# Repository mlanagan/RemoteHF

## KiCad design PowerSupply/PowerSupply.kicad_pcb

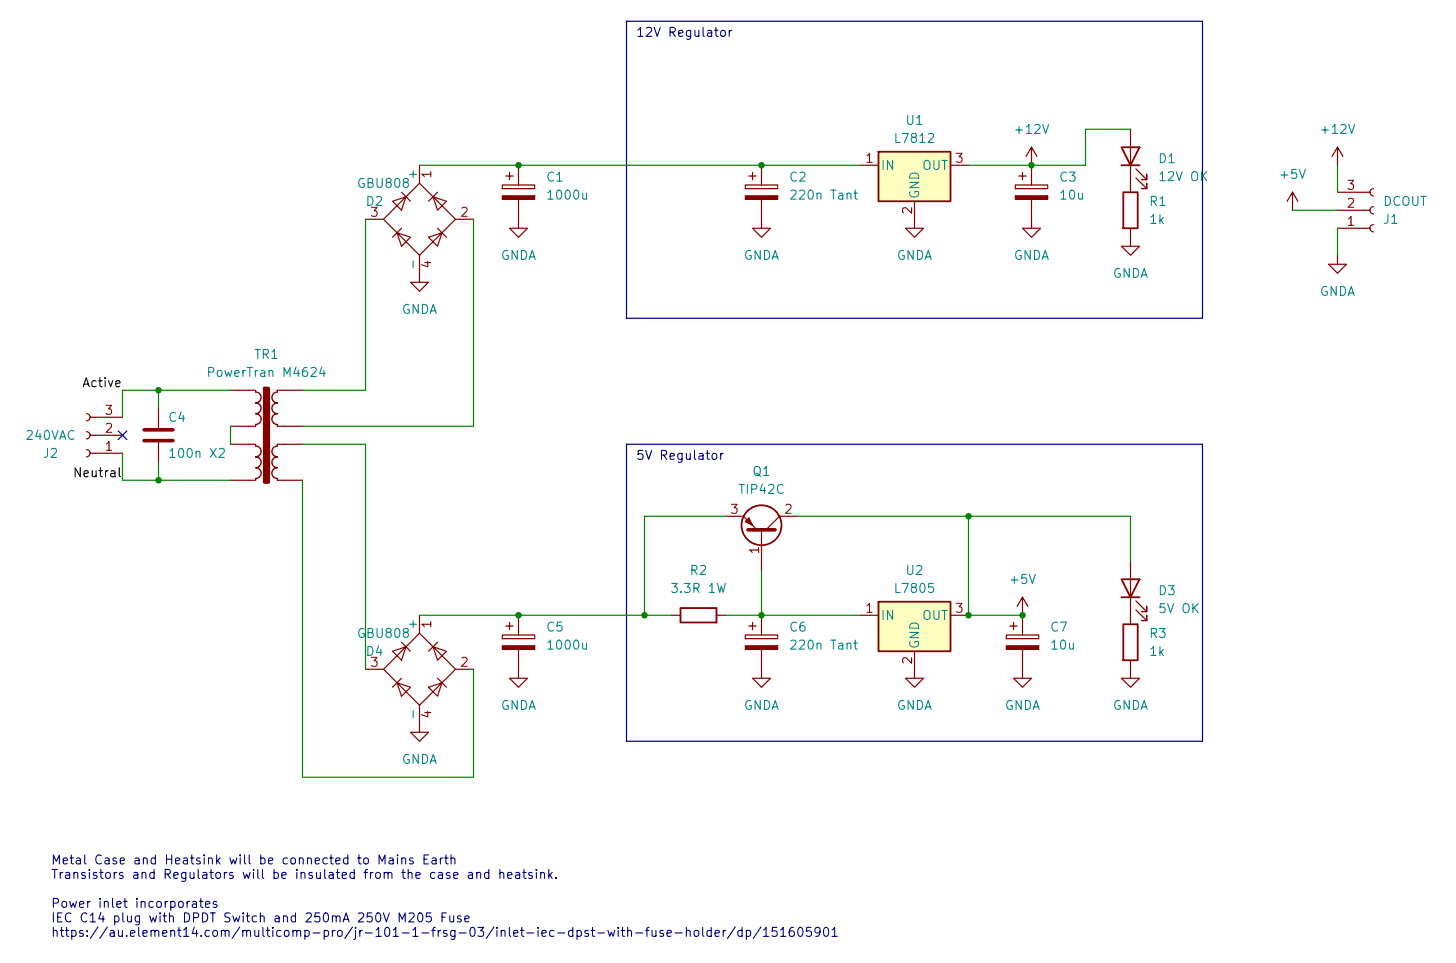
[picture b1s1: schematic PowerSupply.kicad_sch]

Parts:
C1, C5: 1000u; CP_Radial_D13.0mm_P5.00mm
C2, C6: 220n Tant; CP_EIA-3216-18_Kemet-A
C3, C7: 10u; CP_Elec_5x5.7
C4: 100n X2; C_Rect_L18.0mm_W5.0mm_P15.00mm_FKS3_FKP3
D1: 12V OK; LED_0805_2012Metric
D2, D4: GBU808; Diode_Bridge_Vishay_GBU
D3: 5V OK; LED_0805_2012Metric
J1: DCOUT; ScrewTermConnector 1x3
J2: 240VAC; Molex_KK-396_5273-03A_1x03_P3.96mm_Vertical
Q1: TIP42C; TO-220-3_Vertical
R1, R3: 1k; R_0805_2012Metric
R2: 3.3R 1W; R_2512_6332Metric
TR1: PowerTran M4624
U1: L7812; TO-220-3_Vertical
U2: L7805; TO-220-3_Vertical

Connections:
+5V: C7.1, D3.2 (A), J1.2, Q1.2 (C), U2.3 (OUT)
+12V: C3.1, D1.2 (A), J1.3, U1.3 (OUT)
/Active: C4.1, J2.3, TR1.1
/Neutral: C4.2, J2.1, TR1.4
GNDA: C1.2, C2.2, C3.2, C5.2, C6.2, C7.2, D2.4 (-), D4.4 (-), J1.1, R1.2, R3.2, U1.2 (GND), U2.2 (GND)
unnamed: D1.1 (K), R1.1
unnamed: C1.1, C2.1, D2.1 (+), U1.1 (IN)
unnamed: D2.2, TR1.7
unnamed: D2.3, TR1.8
unnamed: D3.1 (K), R3.1
unnamed: C5.1, D4.1 (+), Q1.3 (E), R2.1
unnamed: D4.2, TR1.5
unnamed: D4.3, TR1.6
unnamed: C6.1, Q1.1 (B), R2.2, U2.1 (IN)
unnamed: TR1.2, TR1.3

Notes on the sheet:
Metal Case and Heatsink will be connected to Mains Earth Transistors and Regulators will be insulated from the case and heatsink. Power inlet incorporates IEC C14 plug with DPDT Switch and 250mA 250V M205 Fuse https://au.element14.com/multicomp-pro/jr-101-1-frsg-03/inlet-iec-dpst-with-fuse-holder/d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
12V Regulator
5V Regulator

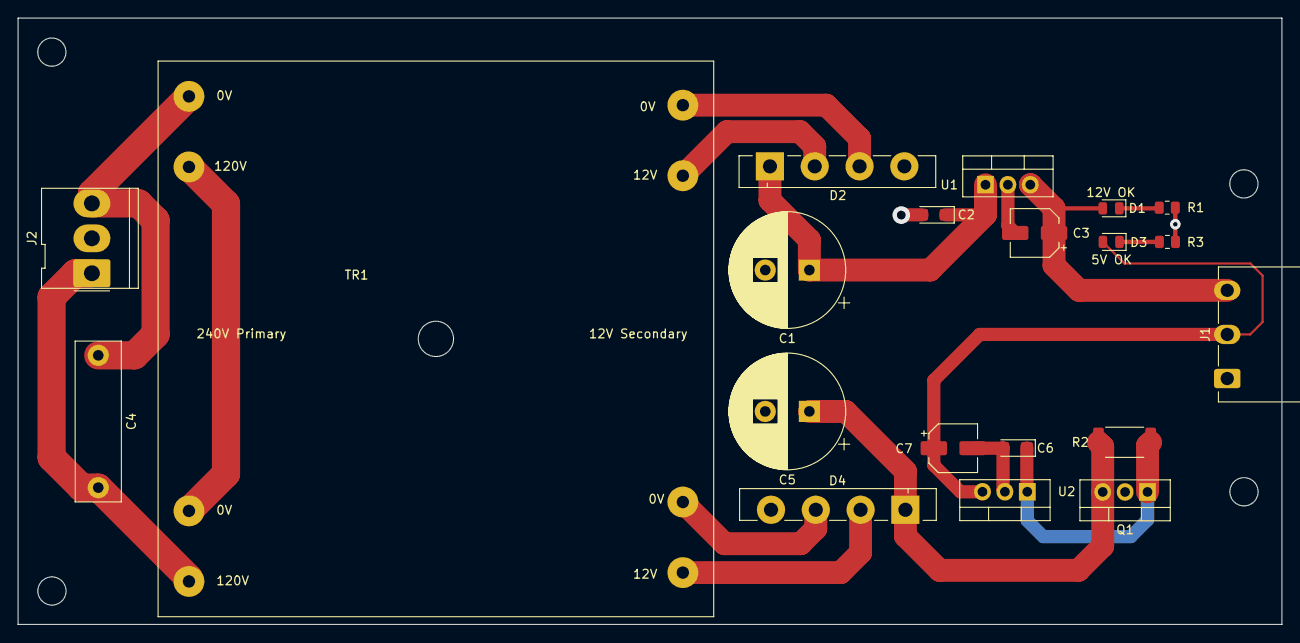
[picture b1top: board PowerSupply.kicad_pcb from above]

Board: 2 copper layers, 143.3 x 68.8 mm, 20 parts (0 on the bottom side), 15 nets.

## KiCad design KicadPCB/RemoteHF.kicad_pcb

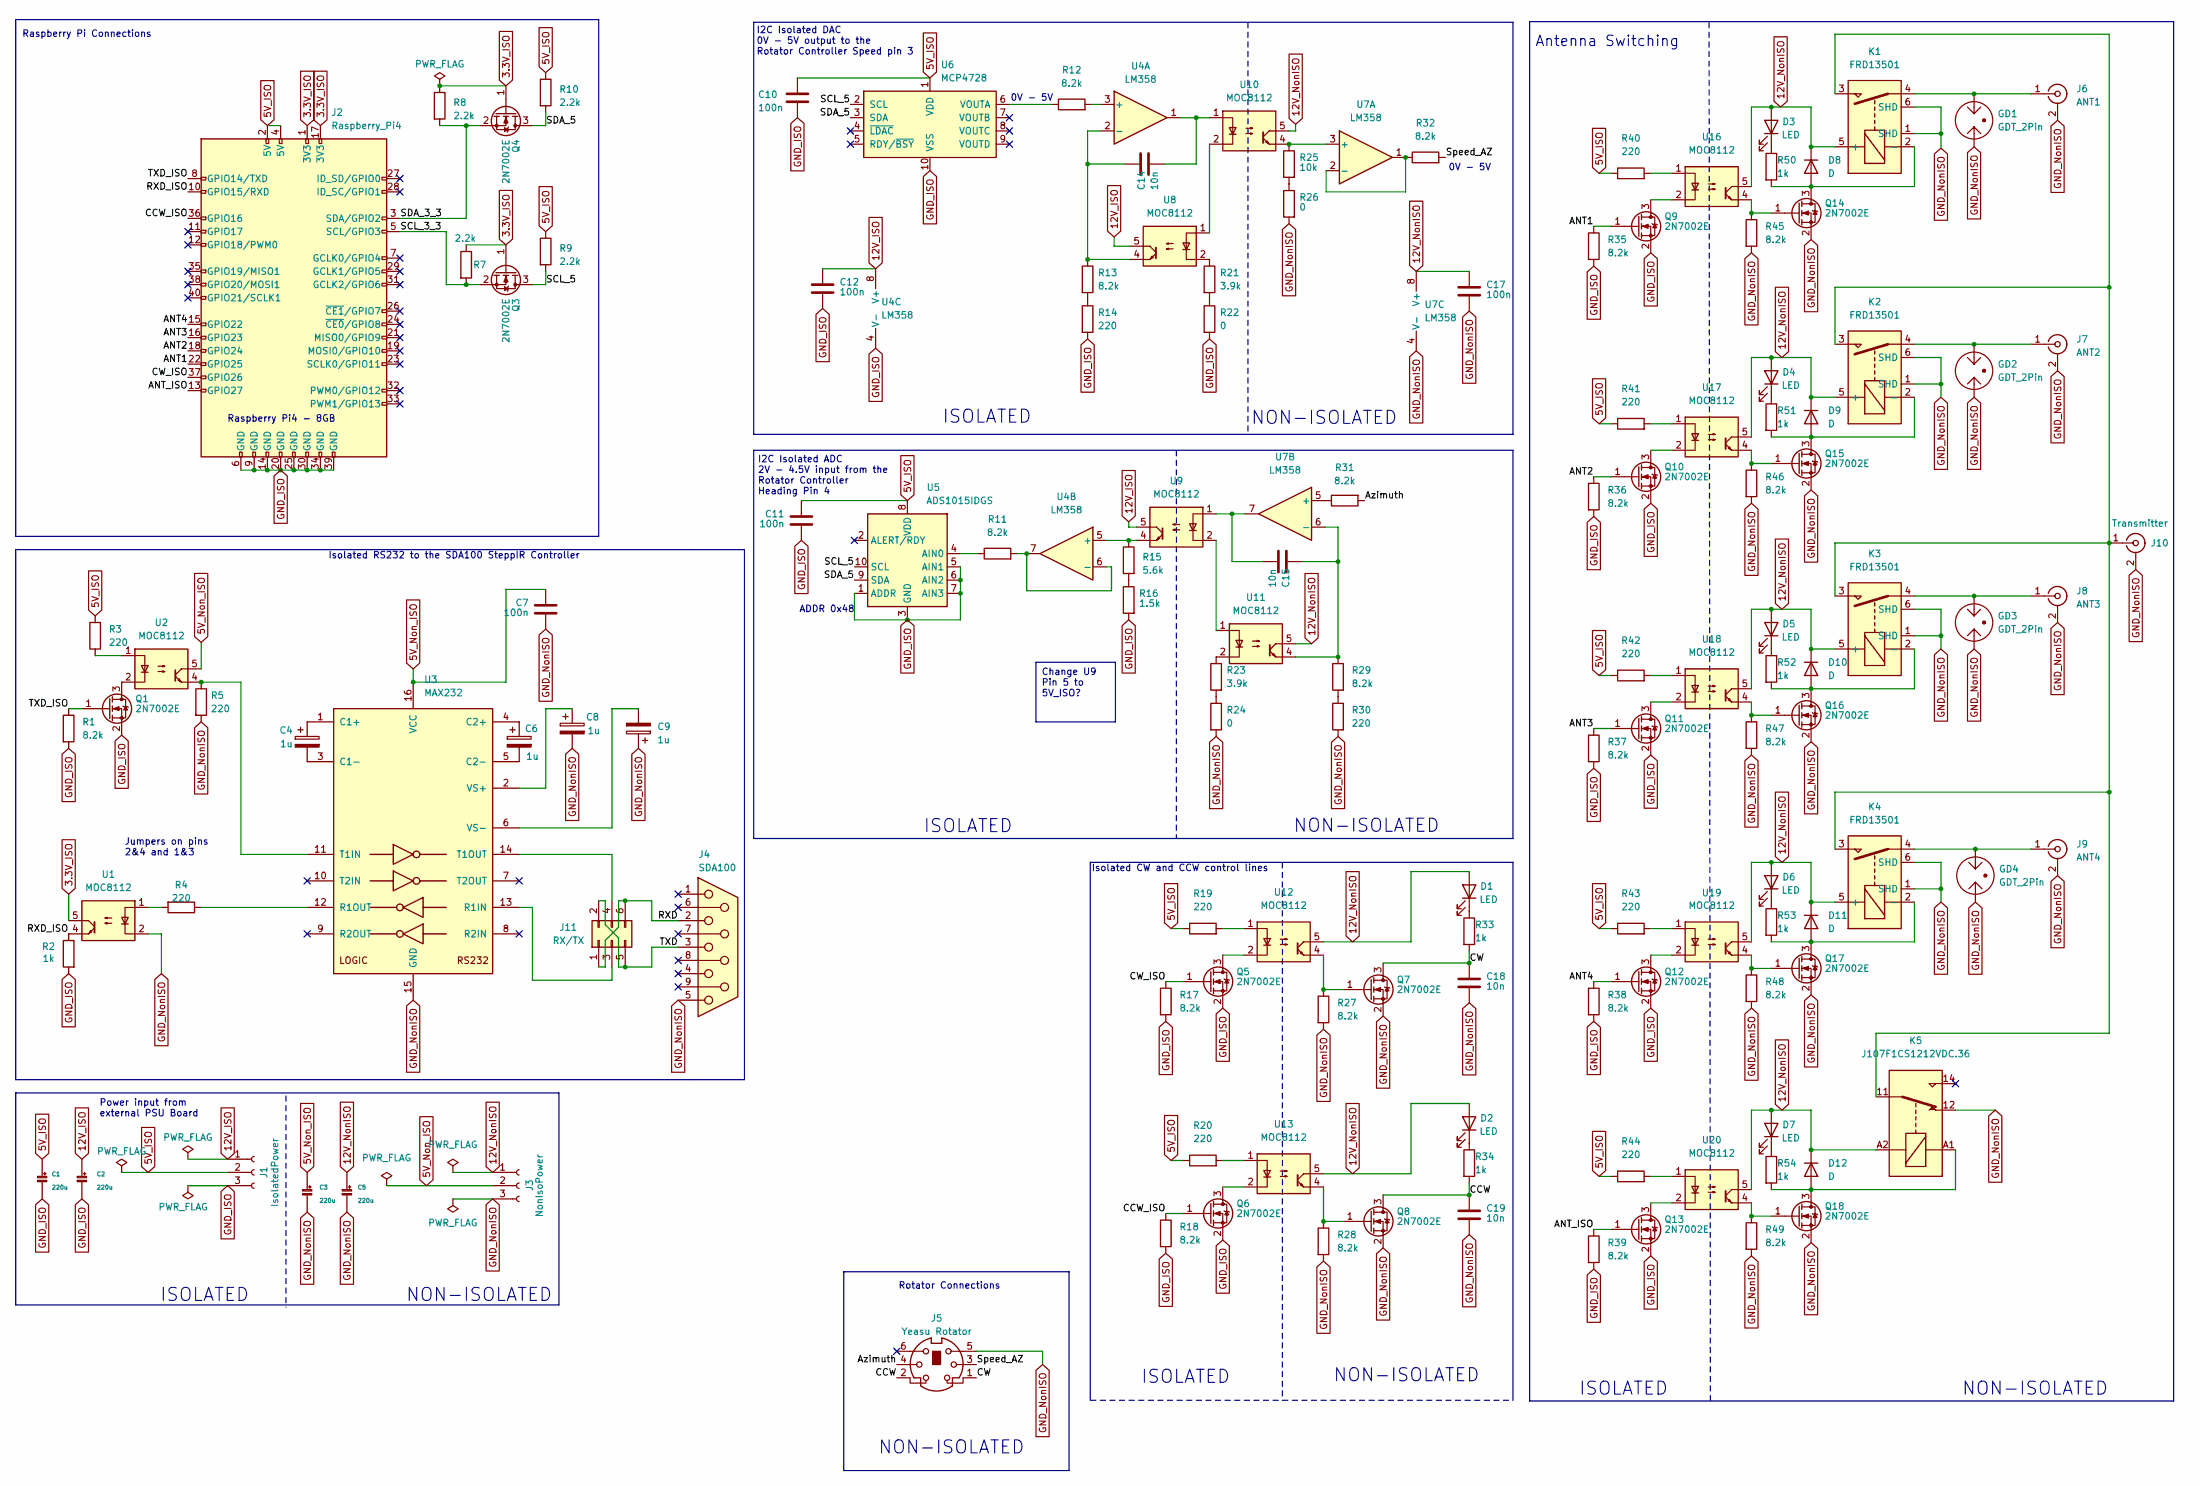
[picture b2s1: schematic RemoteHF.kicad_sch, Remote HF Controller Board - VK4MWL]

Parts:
C1, C2, C3, C5: 220u; CP_Elec_10x10.5
C4, C6, C8, C9: 1u; C_0805_2012Metric
C7, C10, C11, C12, C17: 100n; C_0805_2012Metric
C14, C15, C18, C19: 10n; C_0805_2012Metric
D1, D2, D3, D4, D5, D6, D7: LED; LED_0805_2012Metric
D8, D9, D10, D11, D12: D; D_SOD-123F
GD1, GD2, GD3, GD4: GDT_2Pin; GDT Bourns 2053
J1: IsolatedPower; ScrewTermConnector 1x3
J2: Raspberry_Pi4; Raspberry Pi 4B
J3: NonIsoPower; ScrewTermConnector 1x3
J4: SDA100; DSUB-9_Female_Horizontal_P2.77x2.84mm_EdgePinOffset7.70mm_H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
J5: Yeasu Rotator; Connector_Mini-DIN_Female_6Pin_2rows
J6: ANT1; SMA_Amphenol_901-144_Vertical_Lge
J7: ANT2; SMA_Amphenol_901-144_Vertical_Lge
J8: ANT3; SMA_Amphenol_901-144_Vertical_Lge
J9: ANT4; SMA_Amphenol_901-144_Vertical_Lge
J10: Transmitter; SMA_Amphenol_901-144_Vertical_Lge
J11: RX/TX; PinHeader_2x03_P2.54mm_Vertical
K1, K2, K3, K4: FRD13501; Relay_Crydom_FRD13501
K5: J107F1CS1212VDC.36; Relay_SPDT_Finder_36.11
Q1, Q3, Q4, Q5, Q6, Q7, Q8, Q9, Q10, Q11, Q12, Q13, Q14, Q15, Q16, Q17, Q18: 2N7002E; SOT-23
R1, R11, R12, R13, R17, R18, R27, R28, R29, R31, R32, R35, R36, R37, R38, R39, R45, R46, R47, R48, R49: 8.2k; R_0805_2012Metric
R2, R33, R34, R50, R51, R52, R53, R54: 1k; R_0805_2012Metric
R3, R4, R5, R14, R19, R20, R30, R40, R41, R42, R43, R44: 220; R_0805_2012Metric
R7, R8, R9, R10: 2.2k; R_0805_2012Metric
R15: 5.6k; R_0805_2012Metric
R16: 1.5k; R_0805_2012Metric
R21, R23: 3.9k; R_0805_2012Metric
R22, R24, R26: 0; R_0805_2012Metric
R25: 10k; R_0805_2012Metric
U1, U2, U8, U9, U10, U11, U12, U13, U16, U17, U18, U19, U20: MOC8112; DIP-6_W7.62mm
U3: MAX232; SOP-16_3.9x9.9mm_P1.27mm
U4, U7: LM358; SOIC-8_3.9x4.9mm_P1.27mm
U5: ADS1015IDGS; VSSOP-10_3x3mm_P0.5mm
U6: MCP4728; MSOP-10_3x3mm_P0.5mm

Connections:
3.3V_ISO: J2.1 (3V3), J2.17 (3V3), Q3.1 (G), Q4.1 (G), R7.1, R8.1, U1.5
5V_ISO: C1.1, C10.1, C11.1, J1.2, J2.2 (5V), J2.4 (5V), R3.2, R9.1, R10.1, R19.1, R20.1, R40.1, R41.1, R42.1, R43.1, R44.1, U5.8 (VDD), U6.1 (VDD)
5V_Non_ISO: C3.1, C7.1, J3.2, U2.5, U3.16 (VCC)
12V_ISO: C2.1, C12.1, J1.1, U4.8 (V+), U8.5, U9.5
12V_NonISO: C5.1, C17.1, D1.2 (A), D2.2 (A), D3.2 (A), D4.2 (A), D5.2 (A), D6.2 (A), D7.2 (A), D8.1 (K), D9.1 (K), D10.1 (K), D11.1 (K), D12.1 (K), J3.1, K1.5 (+), K2.5 (+), K3.5 (+), K4.5 (+), K5.A2, U7.8 (V+), U10.5, U11.5, U12.5, U13.5, U16.5, U17.5, U18.5, U19.5, U20.5
/ANT1: J2.22 (GPIO25), Q9.1 (G), R35.1
/ANT2: J2.18 (GPIO24), Q10.1 (G), R36.1
/ANT3: J2.16 (GPIO23), Q11.1 (G), R37.1
/ANT4: J2.15 (GPIO22), Q12.1 (G), R38.1
/ANT_ISO: J2.13 (GPIO27), Q13.1 (G), R39.1
/Azimuth: J5.4, R31.2
/CCW: C19.1, J5.2, Q8.3 (D), R34.2
/CCW_ISO: J2.36 (GPIO16), Q6.1 (G), R18.1
/CW: C18.1, J5.1, Q7.3 (D), R33.2
/CW_ISO: J2.37 (GPIO26), Q5.1 (G), R17.1
/RXD: J4.2, J11.1, J11.6
/RXD_ISO: J2.10 (GPIO15/RXD), R2.1, U1.4
/SCL_3_3: J2.5 (SCL/GPIO3), Q3.2 (S), R7.2
/SCL_5: Q3.3 (D), R9.2, U5.10 (SCL), U6.2 (SCL)
/SDA_3_3: J2.3 (SDA/GPIO2), Q4.2 (S), R8.2
/SDA_5: Q4.3 (D), R10.2, U5.9 (SDA), U6.3 (SDA)
/Speed_AZ: J5.3, R32.2
/TXD: J4.3, J11.2, J11.5
/TXD_ISO: J2.8 (GPIO14/TXD), Q1.1 (G), R1.1
GND_ISO: C1.2, C2.2, C10.2, C11.2, C12.2, J1.3, J2.6 (GND), J2.9 (GND), J2.14 (GND), J2.20 (GND), J2.25 (GND), J2.30 (GND), J2.34 (GND), J2.39 (GND), Q1.2 (S), Q5.2 (S), Q6.2 (S), Q9.2 (S), Q10.2 (S), Q11.2 (S), Q12.2 (S), Q13.2 (S), R1.2, R2.2, R14.2, R16.2, R17.2, R18.2, R22.2, R35.2, R36.2, R37.2, R38.2, R39.2, U4.4 (V-), U5.1 (ADDR), U5.3 (GND), U5.5 (AIN1), U5.6 (AIN2), U5.7 (AIN3), U6.10 (VSS)
GND_NonISO: C3.2, C5.2, C7.2, C8.2, C9.1, C17.2, C18.2, C19.2, GD1.1, GD2.1, GD3.1, GD4.1, J3.3, J4.5, J5.5, J6.2 (Ext), J7.2 (Ext), J8.2 (Ext), J9.2 (Ext), J10.2 (Ext), K1.1 (SHD), K1.6 (SHD), K2.1 (SHD), K2.6 (SHD), K3.1 (SHD), K3.6 (SHD), K4.1 (SHD), K4.6 (SHD), K5.12, Q7.2 (S), Q8.2 (S), Q14.2 (S), Q15.2 (S), Q16.2 (S), Q17.2 (S), Q18.2 (S), R5.2, R24.2, R26.2, R27.2, R28.2, R30.2, R45.2, R46.2, R47.2, R48.2, R49.2, U1.2, U3.15 (GND), U7.4 (V-)
unnamed: C14.2, U4.1, U10.1
unnamed: C15.2, U7.7, U9.1
unnamed: D1.1 (K), R33.1
unnamed: D2.1 (K), R34.1
unnamed: D3.1 (K), R50.1
unnamed: D4.1 (K), R51.1
unnamed: D5.1 (K), R52.1
unnamed: D6.1 (K), R53.1
unnamed: D7.1 (K), R54.1
unnamed: D8.2 (A), K1.2 (-), Q14.3 (D), R50.2
unnamed: D9.2 (A), K2.2 (-), Q15.3 (D), R51.2
unnamed: D10.2 (A), K3.2 (-), Q16.3 (D), R52.2
unnamed: D11.2 (A), K4.2 (-), Q17.3 (D), R53.2
unnamed: D12.2 (A), K5.A1, Q18.3 (D), R54.2
unnamed: GD1.2, J6.1 (In), K1.4
unnamed: GD2.2, J7.1 (In), K2.4
unnamed: GD3.2, J8.1 (In), K3.4
unnamed: GD4.2, J9.1 (In), K4.4
unnamed: J10.1 (In), K1.3, K2.3, K3.3, K4.3, K5.11
unnamed: J11.3, U3.13 (R1IN)
unnamed: J11.4, U3.14 (T1OUT)
unnamed: Q1.3 (D), U2.2
unnamed: Q5.3 (D), U12.2
unnamed: Q6.3 (D), U13.2
unnamed: Q7.1 (G), R27.1, U12.4
unnamed: Q8.1 (G), R28.1, U13.4
unnamed: Q9.3 (D), U16.2
unnamed: Q10.3 (D), U17.2
unnamed: Q11.3 (D), U18.2
unnamed: Q12.3 (D), U19.2
unnamed: Q13.3 (D), U20.2
unnamed: Q14.1 (G), R45.1, U16.4
unnamed: Q15.1 (G), R46.1, U17.4
unnamed: Q16.1 (G), R47.1, U18.4
unnamed: Q17.1 (G), R48.1, U19.4
unnamed: Q18.1 (G), R49.1, U20.4
unnamed: R3.1, U2.1
unnamed: R4.2, U1.1
unnamed: R13.2, R14.1
unnamed: R15.2, R16.1
unnamed: R19.2, U12.1
unnamed: R20.2, U13.1
unnamed: R21.1, U8.2
unnamed: R21.2, R22.1
unnamed: R23.1, U11.2
unnamed: R23.2, R24.1
unnamed: R25.2, R26.1
unnamed: R29.2, R30.1
unnamed: R40.2, U16.1
unnamed: R41.2, U17.1
unnamed: R42.2, U18.1
unnamed: R43.2, U19.1
unnamed: R44.2, U20.1
unnamed: C4.1, U3.1 (C1+)
unnamed: C4.2, U3.3 (C1-)
unnamed: C6.1, U3.4 (C2+)
unnamed: C6.2, U3.5 (C2-)
unnamed: R4.1, U3.12 (R1OUT)
unnamed: R5.1, U2.4, U3.11 (T1IN)
unnamed: C8.1, U3.2 (VS+)
unnamed: C9.2, U3.6 (VS-)
unnamed: R12.2, U4.3 (+)
unnamed: C14.1, R13.1, U4.2 (-), U8.4
unnamed: R15.1, U4.5 (+), U9.4
unnamed: R11.2, U4.6 (-), U4.7
unnamed: R11.1, U5.4 (AIN0)
unnamed: R12.1, U6.6 (VOUTA)
unnamed: R25.1, U7.3 (+), U10.4
unnamed: R32.1, U7.1, U7.2 (-)
unnamed: R31.1, U7.5 (+)
unnamed: C15.1, R29.1, U7.6 (-), U11.4
unnamed: U8.1, U10.2
unnamed: U9.2, U11.1

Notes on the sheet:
Change U9 Pin 5 to 5V_ISO?
ADDR 0x48
Isolated CW and CCW control lines
Isolated RS232 to the SDA100 SteppIR Controller
Antenna Switching
ISOLATED
NON-ISOLATED
Raspberry Pi Connections
0V - 5V
I2C Isolated ADC 2V - 4.5V input from the Rotator Controller Heading Pin 4
Rotator Connections
Power input from external PSU Board
Raspberry Pi4 - 8GB
I2C Isolated DAC 0V - 5V output to the Rotator Controller Speed pin 3
Jumpers on pins 2&4 and 1&3

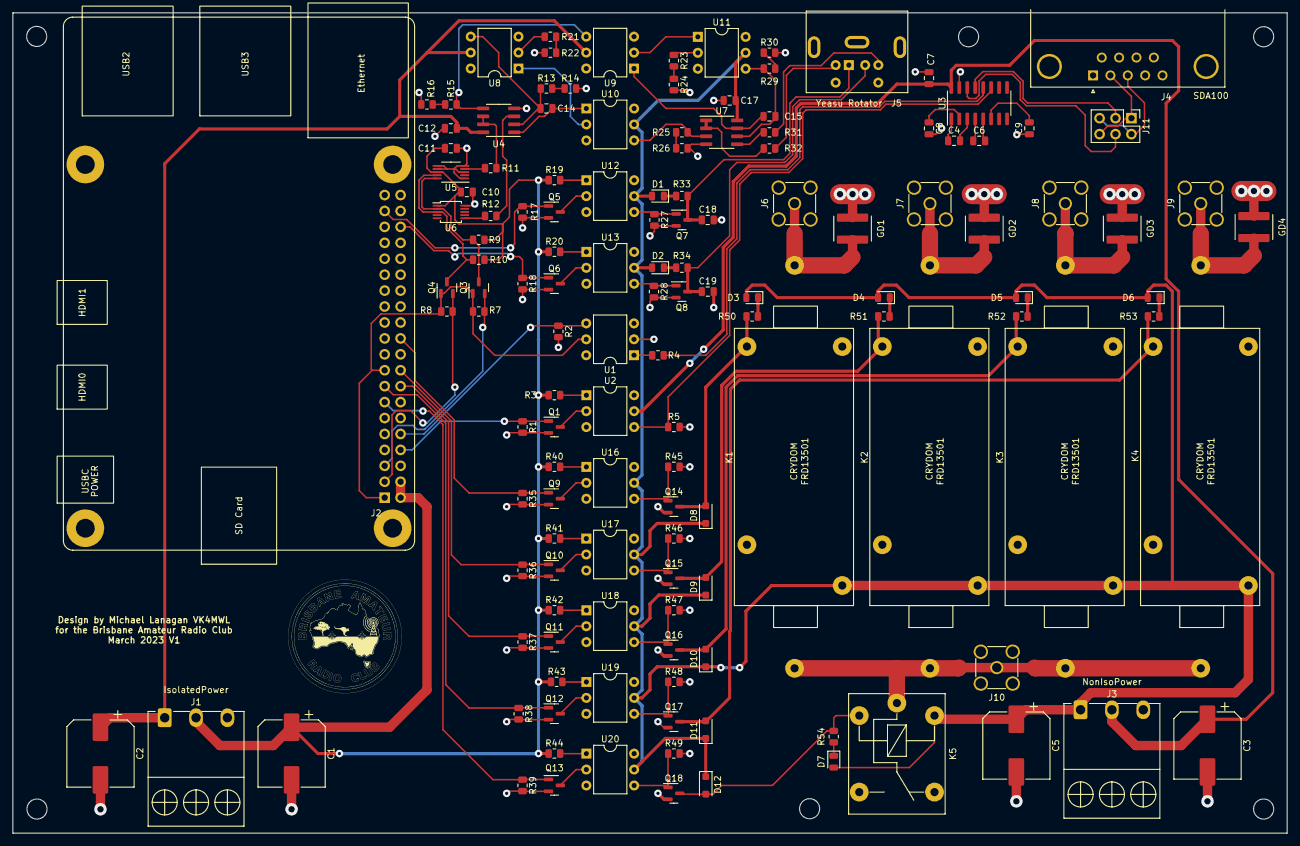
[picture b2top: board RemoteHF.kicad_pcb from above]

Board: 2 copper layers, 203.2 x 130.8 mm, 137 parts (0 on the bottom side), 99 nets.

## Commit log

2023-06-03 Added screen shot of the installed Nodes in Node Red
2023-06-03 Added latest export of NodeRed flow
2023-09-03 Latest Change August 2023 - PowerSupply
2023-09-04 Updated BOM
2023-09-07 Added Power Supply Board
2023-12-27 Updated Node Red JSON
2024-02-25 Updated Node Red with WFView Userlist
2024-03-23 Added control of SteppIR when changing antennas
